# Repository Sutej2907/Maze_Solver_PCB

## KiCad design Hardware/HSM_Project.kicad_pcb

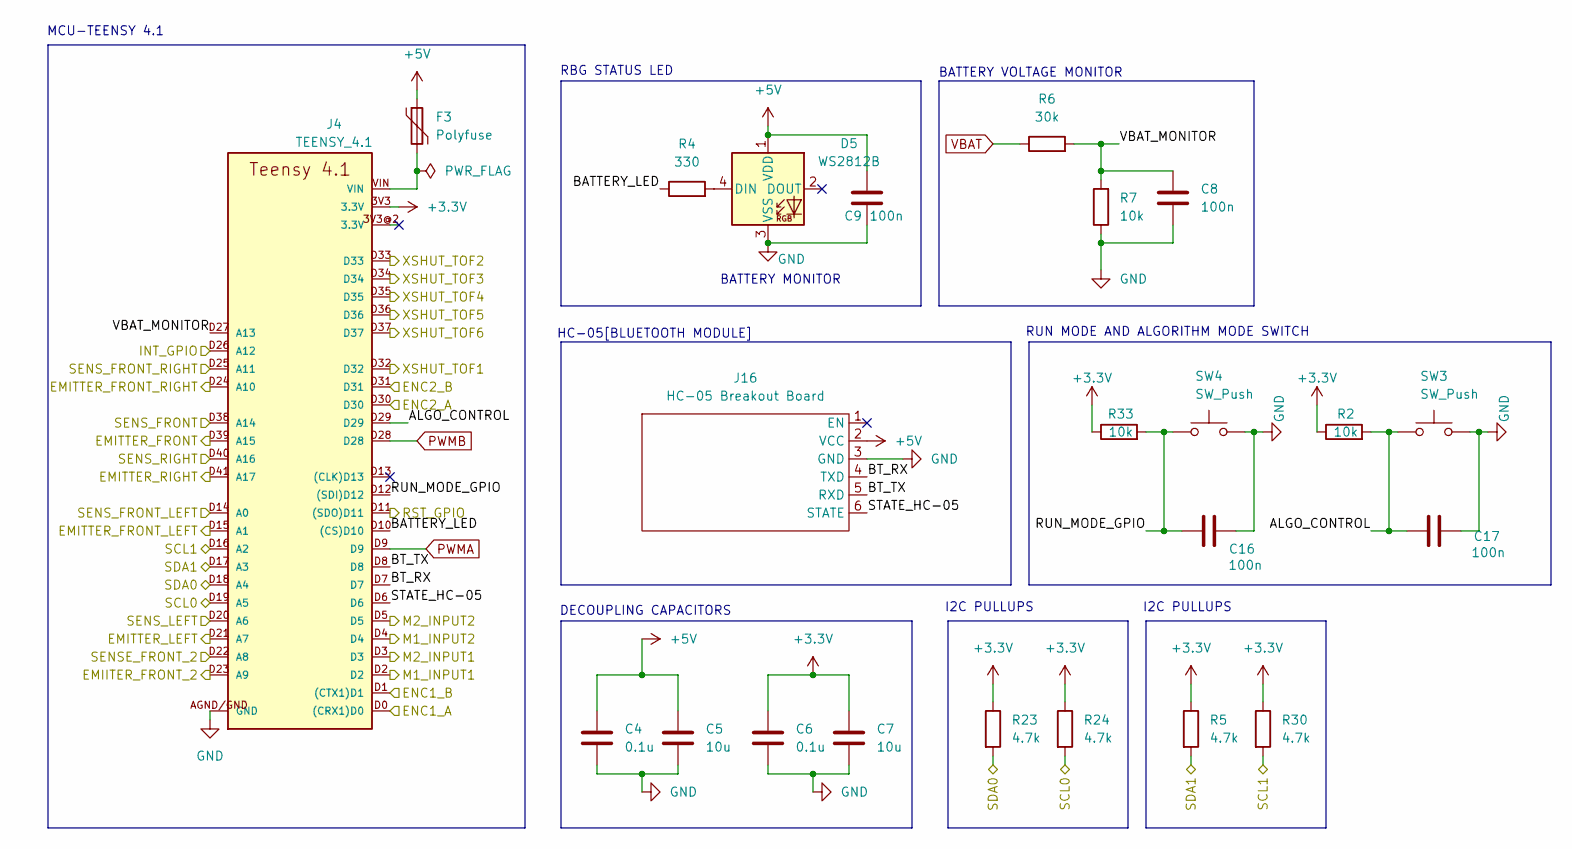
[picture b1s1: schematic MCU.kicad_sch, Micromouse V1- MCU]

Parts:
C4, C6: 0.1u; C_0603_1608Metric_Pad1.08x0.95mm_HandSolder
C5, C7: 10u; C_1210_3225Metric_Pad1.33x2.70mm_HandSolder
C8, C9, C16, C17: 100n; C_0603_1608Metric_Pad1.08x0.95mm_HandSolder
D5: WS2812B; LED_WS2812B_PLCC4_5.0x5.0mm_P3.2mm
F3: Polyfuse; Fuse_0805_2012Metric_Pad1.15x1.40mm_HandSolder
J4: TEENSY_4.1; TEENSY_LONG_EXT
J16: HC-05 Breakout Board; PinSocket_1x06_P2.54mm_Vertical
R2, R7, R33: 10k; R_0603_1608Metric_Pad0.98x0.95mm_HandSolder
R4: 330; R_Axial_DIN0414_L11.9mm_D4.5mm_P15.24mm_Horizontal
R5, R23, R24, R30: 4.7k; R_0603_1608Metric_Pad0.98x0.95mm_HandSolder
R6: 30k; R_0805_2012Metric_Pad1.20x1.40mm_HandSolder
SW3, SW4: SW_Push; Rectangular Tact Button

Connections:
+3.3V: C6.1, C7.1, J4.3V3 (3.3V), R2.1, R5.1, R23.1, R24.1, R30.1, R33.1; also elsewhere on the board
+5V: C4.1, C5.1, C9.1, D5.1 (VDD), F3.1, J16.2 (VCC); also elsewhere on the board
/Control Unit/ALGO_CONTROL: C17.2, J4.D29, R2.2, SW3.1
/Control Unit/BATTERY_LED: J4.D10 ((CS)D10), R4.1
/Control Unit/BT_RX: J4.D7, J16.4 (TXD)
/Control Unit/BT_TX: J4.D8, J16.5 (RXD)
/Control Unit/EMIITER_FRONT_2: J4.D23 (A9); also elsewhere on the board
/Control Unit/EMITTER_FRONT: J4.D39 (A15); also elsewhere on the board
/Control Unit/EMITTER_FRONT_LEFT: J4.D15 (A1); also elsewhere on the board
/Control Unit/EMITTER_FRONT_RIGHT: J4.D24 (A10); also elsewhere on the board
/Control Unit/EMITTER_LEFT: J4.D21 (A7); also elsewhere on the board
/Control Unit/EMITTER_RIGHT: J4.D41 (A17); also elsewhere on the board
/Control Unit/ENC1_A: J4.D0 ((CRX1)D0); also elsewhere on the board
/Control Unit/ENC1_B: J4.D1 ((CTX1)D1); also elsewhere on the board
/Control Unit/ENC2_A: J4.D30; also elsewhere on the board
/Control Unit/ENC2_B: J4.D31; also elsewhere on the board
/Control Unit/INT_GPIO: J4.D26 (A12); also elsewhere on the board
/Control Unit/M1_INPUT1: J4.D2; also elsewhere on the board
/Control Unit/M1_INPUT2: J4.D4; also elsewhere on the board
/Control Unit/M2_INPUT1: J4.D3; also elsewhere on the board
/Control Unit/M2_INPUT2: J4.D5; also elsewhere on the board
/Control Unit/RST_GPIO: J4.D11 ((SDO)D11); also elsewhere on the board
/Control Unit/RUN_MODE_GPIO: C16.2, J4.D12 ((SDI)D12), R33.2, SW4.1
/Control Unit/SCL0: J4.D19 (A5), R24.2; also elsewhere on the board
/Control Unit/SCL1: J4.D16 (A2), R30.2; also elsewhere on the board
/Control Unit/SDA0: J4.D18 (A4), R23.2; also elsewhere on the board
/Control Unit/SDA1: J4.D17 (A3), R5.2; also elsewhere on the board
/Control Unit/SENSE_FRONT_2: J4.D22 (A8); also elsewhere on the board
/Control Unit/SENS_FRONT: J4.D38 (A14); also elsewhere on the board
/Control Unit/SENS_FRONT_LEFT: J4.D14 (A0); also elsewhere on the board
/Control Unit/SENS_FRONT_RIGHT: J4.D25 (A11); also elsewhere on the board
/Control Unit/SENS_LEFT: J4.D20 (A6); also elsewhere on the board
/Control Unit/SENS_RIGHT: J4.D40 (A16); also elsewhere on the board
/Control Unit/STATE_HC-05: J4.D6, J16.6 (STATE)
/Control Unit/VBAT_MONITOR: C8.1, J4.D27 (A13), R6.2, R7.2
/Control Unit/XSHUT_TOF1: J4.D32; also elsewhere on the board
/Control Unit/XSHUT_TOF2: J4.D33; also elsewhere on the board
/Control Unit/XSHUT_TOF3: J4.D34; also elsewhere on the board
/Control Unit/XSHUT_TOF4: J4.D35; also elsewhere on the board
/Control Unit/XSHUT_TOF5: J4.D36; also elsewhere on the board
/Control Unit/XSHUT_TOF6: J4.D37; also elsewhere on the board
GND: C4.2, C5.2, C6.2, C7.2, C8.2, C9.2, C16.1, C17.1, D5.3 (VSS), J4.AGND/GND (GND), J4.GND, J4.GND@2 (GND), J16.3 (GND), R7.1, SW3.2, SW4.2; also elsewhere on the board
unnamed: D5.4 (DIN), R4.2
unnamed: F3.2, J4.VIN
PWMA: J4.D9; also elsewhere on the board
PWMB: J4.D28; also elsewhere on the board
VBAT: R6.1; also elsewhere on the board

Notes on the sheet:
RBG STATUS LED
DECOUPLING CAPACITORS
I2C PULLUPS
MCU-TEENSY 4.1
BATTERY VOLTAGE MONITOR
BATTERY MONITOR
RUN MODE AND ALGORITHM MODE SWITCH
HC-05[BLUETOOTH MODULE]

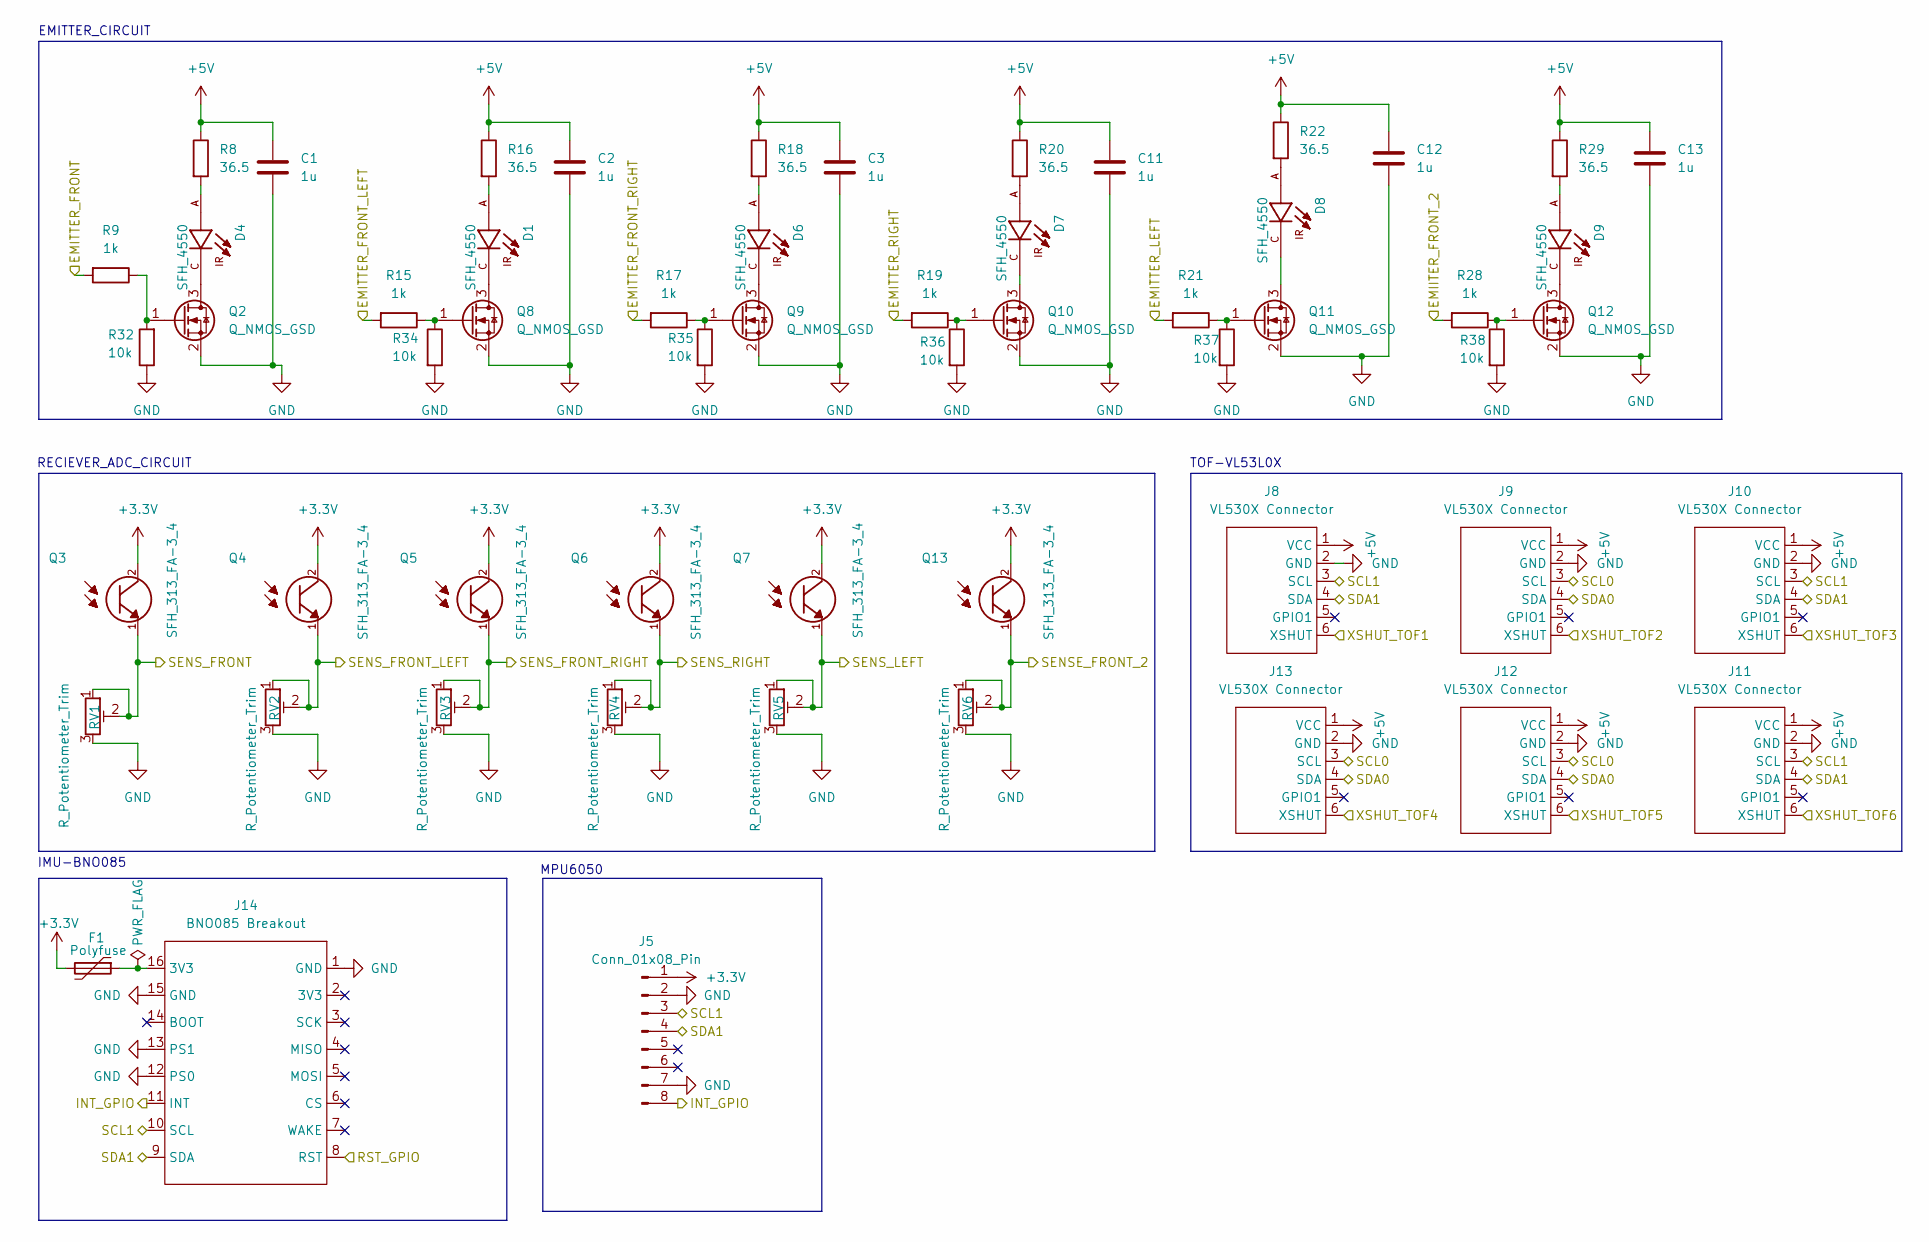
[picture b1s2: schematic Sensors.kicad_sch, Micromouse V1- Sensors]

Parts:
C1, C2, C3, C11, C12, C13: 1u; C_0603_1608Metric_Pad1.08x0.95mm_HandSolder
D1, D4, D6, D7, D8, D9: SFH_4550; DIO_SFH_4550; PARTREV 1.6
F1: Polyfuse; Fuse_0805_2012Metric_Pad1.15x1.40mm_HandSolder
J5: Conn_01x08_Pin; PinSocket_1x08_P2.54mm_Vertical
J8, J9, J10, J11, J12, J13: VL530X Connector; PinSocket_1x06_P2.54mm_Vertical
J14: BNO085 Breakout; BNO085
Q2, Q8, Q9, Q10, Q11, Q12: Q_NMOS_GSD; SOT-23
Q3, Q4, Q5, Q6, Q7, Q13: SFH_313_FA-3_4; XDCR_SFH_313_FA-3_4; PARTREV 1.3
R8, R16, R18, R20, R22, R29: 36.5; R_1210_3225Metric_Pad1.30x2.65mm_HandSolder
R9, R15, R17, R19, R21, R28: 1k; R_0603_1608Metric_Pad0.98x0.95mm_HandSolder
R32, R34, R35, R36, R37, R38: 10k; R_0603_1608Metric_Pad0.98x0.95mm_HandSolder
RV1, RV2, RV3, RV4, RV5, RV6: R_Potentiometer_Trim; Potentiometer_Bourns_3296W_Vertical

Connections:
+3.3V: F1.2, J5.1, Q3.2, Q4.2, Q5.2, Q6.2, Q7.2, Q13.2; also elsewhere on the board
+5V: C1.1, C2.1, C3.1, C11.1, C12.1, C13.1, J8.1 (VCC), J9.1 (VCC), J10.1 (VCC), J11.1 (VCC), J12.1 (VCC), J13.1 (VCC), R8.1, R16.1, R18.1, R20.1, R22.1, R29.1; also elsewhere on the board
/Control Unit/EMIITER_FRONT_2: R28.2; also elsewhere on the board
/Control Unit/EMITTER_FRONT: R9.2; also elsewhere on the board
/Control Unit/EMITTER_FRONT_LEFT: R15.2; also elsewhere on the board
/Control Unit/EMITTER_FRONT_RIGHT: R17.2; also elsewhere on the board
/Control Unit/EMITTER_LEFT: R21.2; also elsewhere on the board
/Control Unit/EMITTER_RIGHT: R19.2; also elsewhere on the board
/Control Unit/INT_GPIO: J5.8, J14.11 (INT); also elsewhere on the board
/Control Unit/RST_GPIO: J14.8 (RST); also elsewhere on the board
/Control Unit/SCL0: J9.3 (SCL), J12.3 (SCL), J13.3 (SCL); also elsewhere on the board
/Control Unit/SCL1: J5.3, J8.3 (SCL), J10.3 (SCL), J11.3 (SCL), J14.10 (SCL); also elsewhere on the board
/Control Unit/SDA0: J9.4 (SDA), J12.4 (SDA), J13.4 (SDA); also elsewhere on the board
/Control Unit/SDA1: J5.4, J8.4 (SDA), J10.4 (SDA), J11.4 (SDA), J14.9 (SDA); also elsewhere on the board
/Control Unit/SENSE_FRONT_2: Q13.1, RV6.1, RV6.2; also elsewhere on the board
/Control Unit/SENS_FRONT: Q3.1, RV1.1, RV1.2; also elsewhere on the board
/Control Unit/SENS_FRONT_LEFT: Q4.1, RV2.1, RV2.2; also elsewhere on the board
/Control Unit/SENS_FRONT_RIGHT: Q5.1, RV3.1, RV3.2; also elsewhere on the board
/Control Unit/SENS_LEFT: Q7.1, RV5.1, RV5.2; also elsewhere on the board
/Control Unit/SENS_RIGHT: Q6.1, RV4.1, RV4.2; also elsewhere on the board
/Control Unit/XSHUT_TOF1: J8.6 (XSHUT); also elsewhere on the board
/Control Unit/XSHUT_TOF2: J9.6 (XSHUT); also elsewhere on the board
/Control Unit/XSHUT_TOF3: J10.6 (XSHUT); also elsewhere on the board
/Control Unit/XSHUT_TOF4: J13.6 (XSHUT); also elsewhere on the board
/Control Unit/XSHUT_TOF5: J12.6 (XSHUT); also elsewhere on the board
/Control Unit/XSHUT_TOF6: J11.6 (XSHUT); also elsewhere on the board
GND: C1.2, C2.2, C3.2, C11.2, C12.2, C13.2, J5.2, J5.7, J8.2 (GND), J9.2 (GND), J10.2 (GND), J11.2 (GND), J12.2 (GND), J13.2 (GND), J14.1 (GND), J14.12 (PS0), J14.13 (PS1), J14.15 (GND), Q2.2 (S), Q8.2 (S), Q9.2 (S), Q10.2 (S), Q11.2 (S), Q12.2 (S), R32.1, R34.2, R35.2, R36.2, R37.2, R38.2, RV1.3, RV2.3, RV3.3, RV4.3, RV5.3, RV6.3; also elsewhere on the board
unnamed: D1.A, R16.2
unnamed: D4.A, R8.2
unnamed: D6.A, R18.2
unnamed: D7.A, R20.2
unnamed: D8.A, R22.2
unnamed: D9.A, R29.2
unnamed: F1.1, J14.16 (3V3)
unnamed: D4.C, Q2.3 (D)
unnamed: Q2.1 (G), R9.1, R32.2
unnamed: D1.C, Q8.3 (D)
unnamed: Q8.1 (G), R15.1, R34.1
unnamed: D6.C, Q9.3 (D)
unnamed: Q9.1 (G), R17.1, R35.1
unnamed: D7.C, Q10.3 (D)
unnamed: Q10.1 (G), R19.1, R36.1
unnamed: D8.C, Q11.3 (D)
unnamed: Q11.1 (G), R21.1, R37.1
unnamed: D9.C, Q12.3 (D)
unnamed: Q12.1 (G), R28.1, R38.1

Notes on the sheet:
MPU6050
RECIEVER_ADC_CIRCUIT
IMU-BNO085
EMITTER_CIRCUIT
TOF-VL53L0X

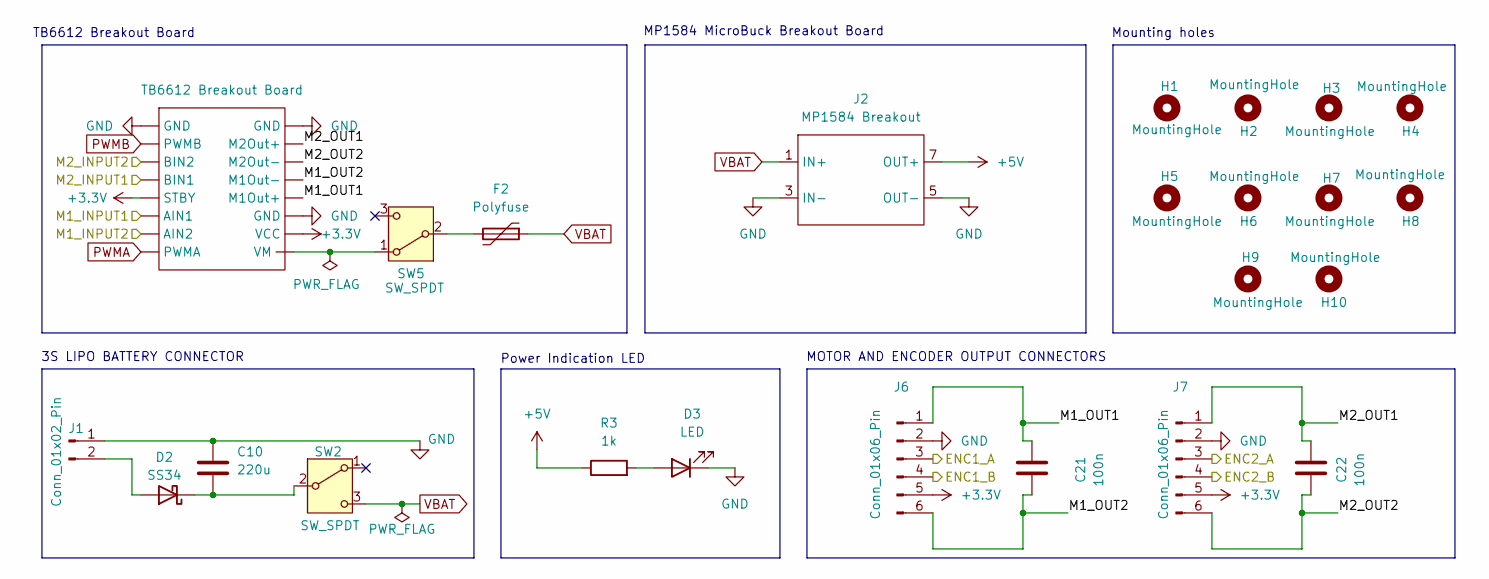
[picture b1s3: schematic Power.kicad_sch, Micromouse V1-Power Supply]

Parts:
C10: 220u; CP_Radial_D6.3mm_P2.50mm
C21, C22: 100n; C_0603_1608Metric_Pad1.08x0.95mm_HandSolder
D2: SS34; D_SMA_Handsoldering
D3: LED; LED_D3.0mm_micromouse
F2: Polyfuse; Fuse_Bourns_MF-SM_9.5x6.71mm
H1, H2, H3, H4, H5, H6, H7, H8: MountingHole; MountingHole_2.2mm_M2
H9, H10: MountingHole; MountingHole_3.2mm_M3
J1: Conn_01x02_Pin; AMASS_XT30UPB-M_1x02_P5.0mm_Vertical
J2: MP1584 Breakout; MP1584
J6, J7: Conn_01x06_Pin; JST_PH_B6B-PH-K_1x06_P2.00mm_Vertical
R3: 1k; R_0603_1608Metric_Pad0.98x0.95mm_HandSolder
SW2, SW5: SW_SPDT; SW_Slide_SPDT_Angled_CK_OS102011MA1Q
TB1: TB6612 Breakout Board; TB6612 module

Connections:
+3.3V: J6.5, J7.5, TB1.5 (STBY), TB1.15 (VCC); also elsewhere on the board
+5V: J2.7 (OUT+), J2.8 (OUT+), R3.1; also elsewhere on the board
/Control Unit/ENC1_A: J6.3; also elsewhere on the board
/Control Unit/ENC1_B: J6.4; also elsewhere on the board
/Control Unit/ENC2_A: J7.3; also elsewhere on the board
/Control Unit/ENC2_B: J7.4; also elsewhere on the board
/Control Unit/M1_INPUT1: TB1.6 (AIN1); also elsewhere on the board
/Control Unit/M1_INPUT2: TB1.7 (AIN2); also elsewhere on the board
/Control Unit/M2_INPUT1: TB1.4 (BIN1); also elsewhere on the board
/Control Unit/M2_INPUT2: TB1.3 (BIN2); also elsewhere on the board
/Power Unit/M1_OUT1: C21.2, J6.1, TB1.13 (M1Out+)
/Power Unit/M1_OUT2: C21.1, J6.6, TB1.12 (M1Out-)
/Power Unit/M2_OUT1: C22.2, J7.1, TB1.10 (M2Out+)
/Power Unit/M2_OUT2: C22.1, J7.6, TB1.11 (M2Out-)
GND: C10.1, D3.1 (K), J1.1, J2.3 (IN-), J2.4 (IN-), J2.5 (OUT-), J2.6 (OUT-), J6.2, J7.2, TB1.1 (GND), TB1.9 (GND), TB1.14 (GND); also elsewhere on the board
unnamed: D2.2 (A), J1.2
unnamed: C10.2, D2.1 (K), SW2.2 (B)
unnamed: D3.2 (A), R3.2
unnamed: SW5.1 (A), TB1.16 (VM)
unnamed: F2.2, SW5.2 (B)
PWMA: TB1.8 (PWMA); also elsewhere on the board
PWMB: TB1.2 (PWMB); also elsewhere on the board
VBAT: F2.1, J2.1 (IN+), J2.2 (IN+), SW2.3 (C); also elsewhere on the board

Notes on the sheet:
Mounting holes
MOTOR AND ENCODER OUTPUT CONNECTORS
TB6612 Breakout Board
Power Indication LED
MP1584 MicroBuck Breakout Board
3S LIPO BATTERY CONNECTOR

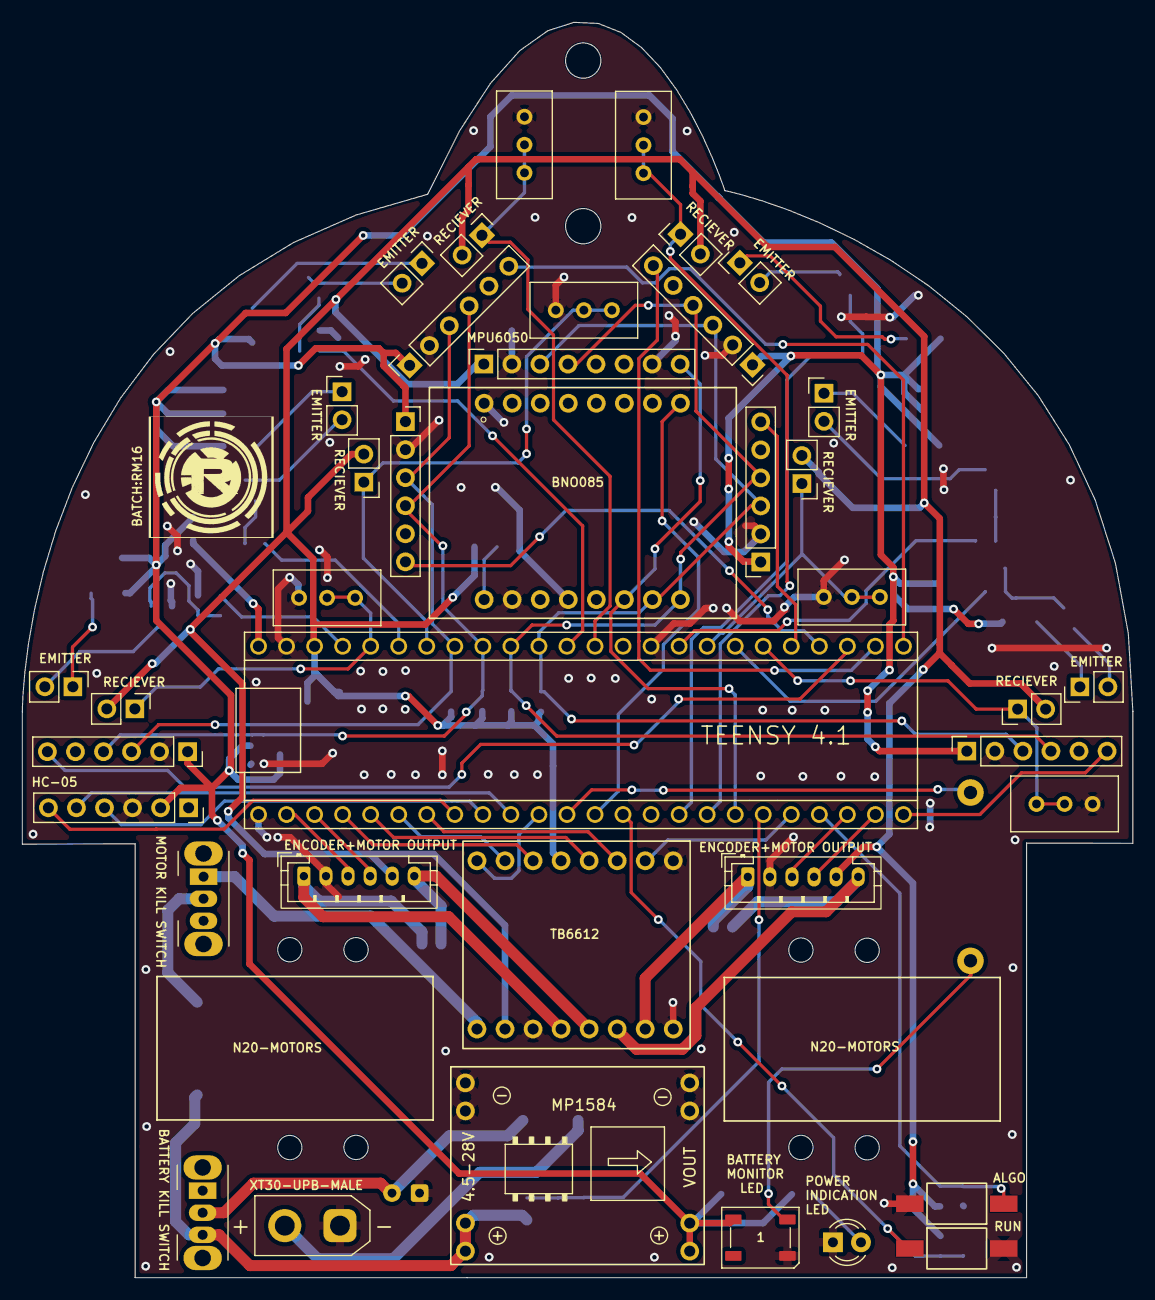
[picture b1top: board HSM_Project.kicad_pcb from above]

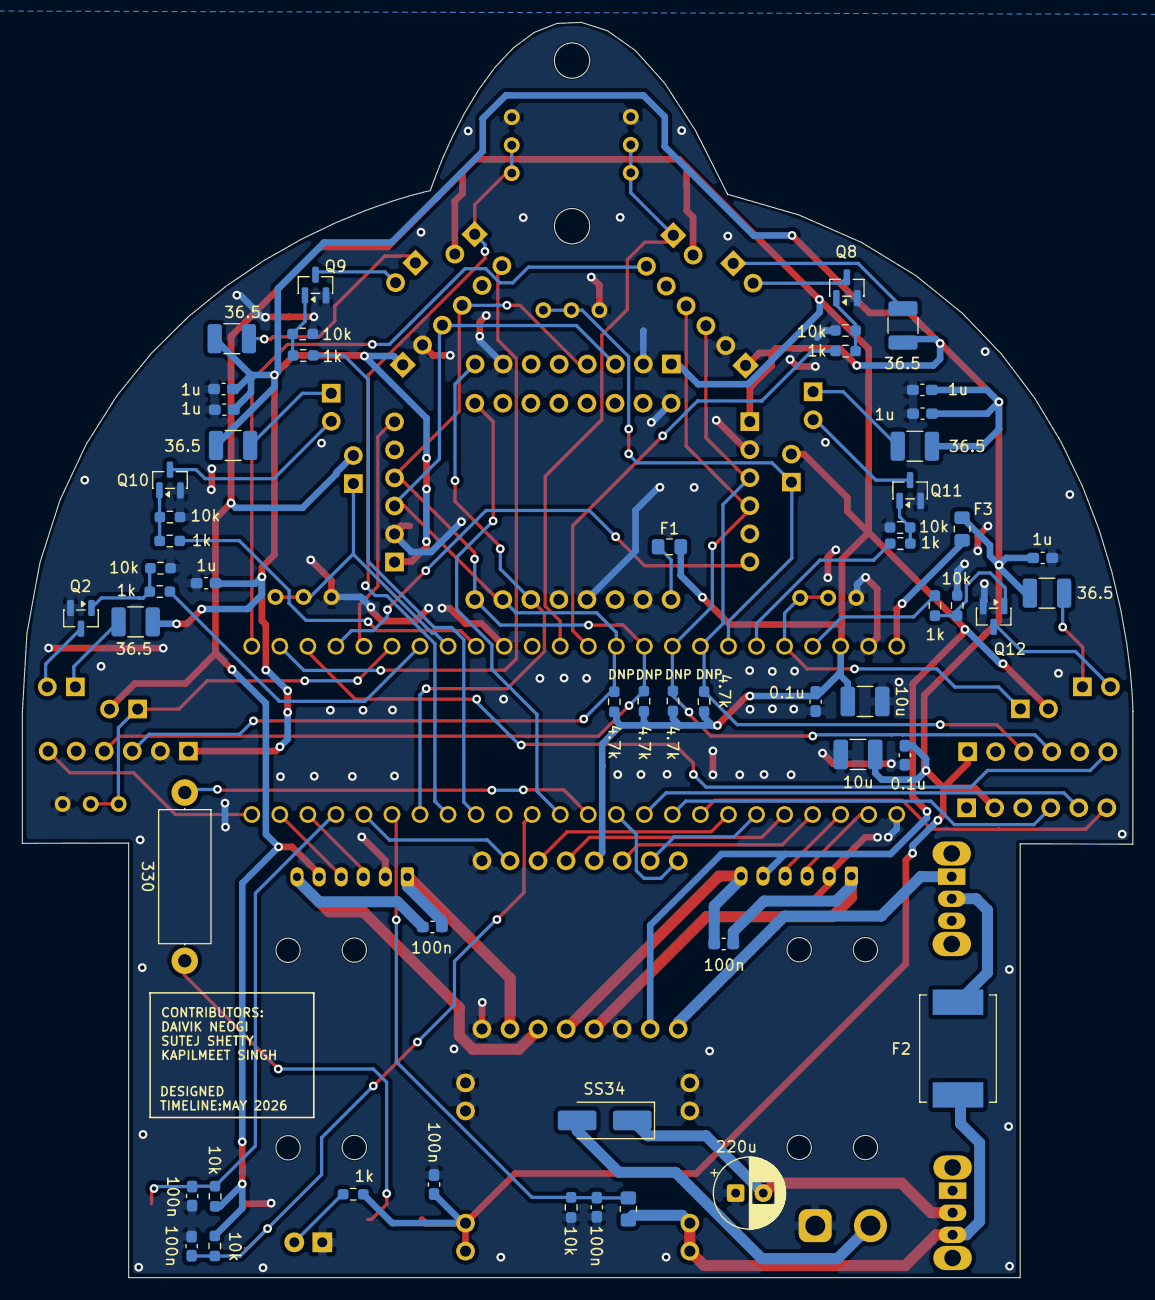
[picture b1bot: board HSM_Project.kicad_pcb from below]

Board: 2 copper layers, 100.6 x 113.7 mm, 104 parts (55 on the bottom side), 75 nets.

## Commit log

2026-04-07 Updated the sensor sheet by adding soldern jumpers for xshut for tof sensors, also corrected the motor sheet and mcu sheet
2026-04-07 Created Hardware folder
2026-04-08 Reorganized project into folders
2026-04-08 Added .gitignore for KiCad project
2026-04-08 Removed unwanted files from tracking
2026-04-08 Completed schematic design
2026-04-08 Schematic updated with buck and motor driver breakout boards
2026-04-12 Switches changed,added low pass filters, emitter caps
2026-04-14 Added KiCad PCB files
2026-04-17 Added the mounting holes, kill iwtch for the moto,removed resistors from xshut, and some others
2026-04-18 1)PCB tracing continued, power traces need to verified,signal traces almost done except xshut, need to verify drv8833 dimesnions, should resolve teensy 4.1 error, switches footprint need to be change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
2026-04-19 PCB tracing, rectified most of the errors and warnings in drc,updated the drv8833 footprint and have to replace it will old footprint in the pcb, need to rectify the little left over error[4] and war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
2026-05-01 Final updated pcb and schematic before dfm check
2026-05-01 Final schematic and pcb before dfm check
2026-05-02 Ignore KiCad .history folder
2026-05-02 Removed KiCad .history folder completely
2026-05-21 updated the dimensiosn of tb6612,shifted placements based on dfm check, other changes
2026-05-21 Ignore KiCad backup zip files
2026-05-21 Ignore KiCad temp files
2026-05-21 Removed tracked KiCad temp files
2026-05-21 Clean up .gitignore
2026-05-27 Updated PCB files after dfm check
2026-05-28 Made changes with i2c bus, added state connection and removed en of hc05, added bno085 fuse,bno085 2nd 3v3 unconnected flag has been put, reversed the connection for battery connector based on the xt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
2026-05-28 Added KiCad backup files
2026-05-28 Removed KiCad .history folder from tracking
2026-05-28 Clean repository and ignore KiCad temp/history files
2026-06-01 Updated the ootprint of emitter and reciver to pinheader, largened the logo
2026-06-01 Clean repository and update PCB design
2026-06-01 Update gitignore and PCB files
2026-06-01 Fix gitignore encoding
